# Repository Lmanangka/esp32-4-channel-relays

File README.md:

# PCB Design for 4-Channel Relays Based on ESP32-WROOM-32 Module

This repository contains the PCB design files, schematic, and 3D model image
for a 4-channel relay board based on the ESP32-WROOM-32 module. The board is
designed for controlling various electronic devices such as light, fans,
motors, and more.

## Features

- Four independently controllable 5V relays.
- ESP32-WROOM-32 module for wireless connectivity and easy programming.
- Terminal block for easy integration to the electronic devices.
- USB TYPE-C connector for power and programming
- Small form factor for easy integration into any project.

## Repository Contents

- **PCB design files**: The KiCad project files for the PCB design.
- **Schematic**: The circuit diagram of the design.
- **3D model image**: A preview image of the 3D model of the board.

## PCB Design

The PCB design is created using KiCad, an open-source software suite for
electronic design automation(EDA). The design files include the Schematic, the
PCB layout, and the Gerber files required for manufacturing.

The board include four 5V relays, each of which is controlled by a GPIO pin of
the ESP32-WROOM-32 module. The module is also responsible for wireless
connectivity and easy programming of the board. Terminal blocks are provided
for easy connection to the electronic devices. The board also includes a USB
TYPE-C connector for power and programming, providing a more robust and
versatile interface than traditional USB connectors.

## Schematic

The Schematic shows the circuit diagram of the design, including the
ESP32-WROOM-32 module, the relays, and the other components of the board.

## 3D Model Image

The 3D model image provides a preview of what the board looks like in a 3D view.
This can be usefule for visualizing the board and how it will fit into your
project.

## License

This design is released under the CERN Open Hardware License Version 2 - Permissive.
You are free to use, modify, and distribute the design as long as you include
the license file in your distribution. See the [LICENSE](https://github.com/Lmanangka/esp32-4-channel-relays/blob/main/LICENSE)
file for details.

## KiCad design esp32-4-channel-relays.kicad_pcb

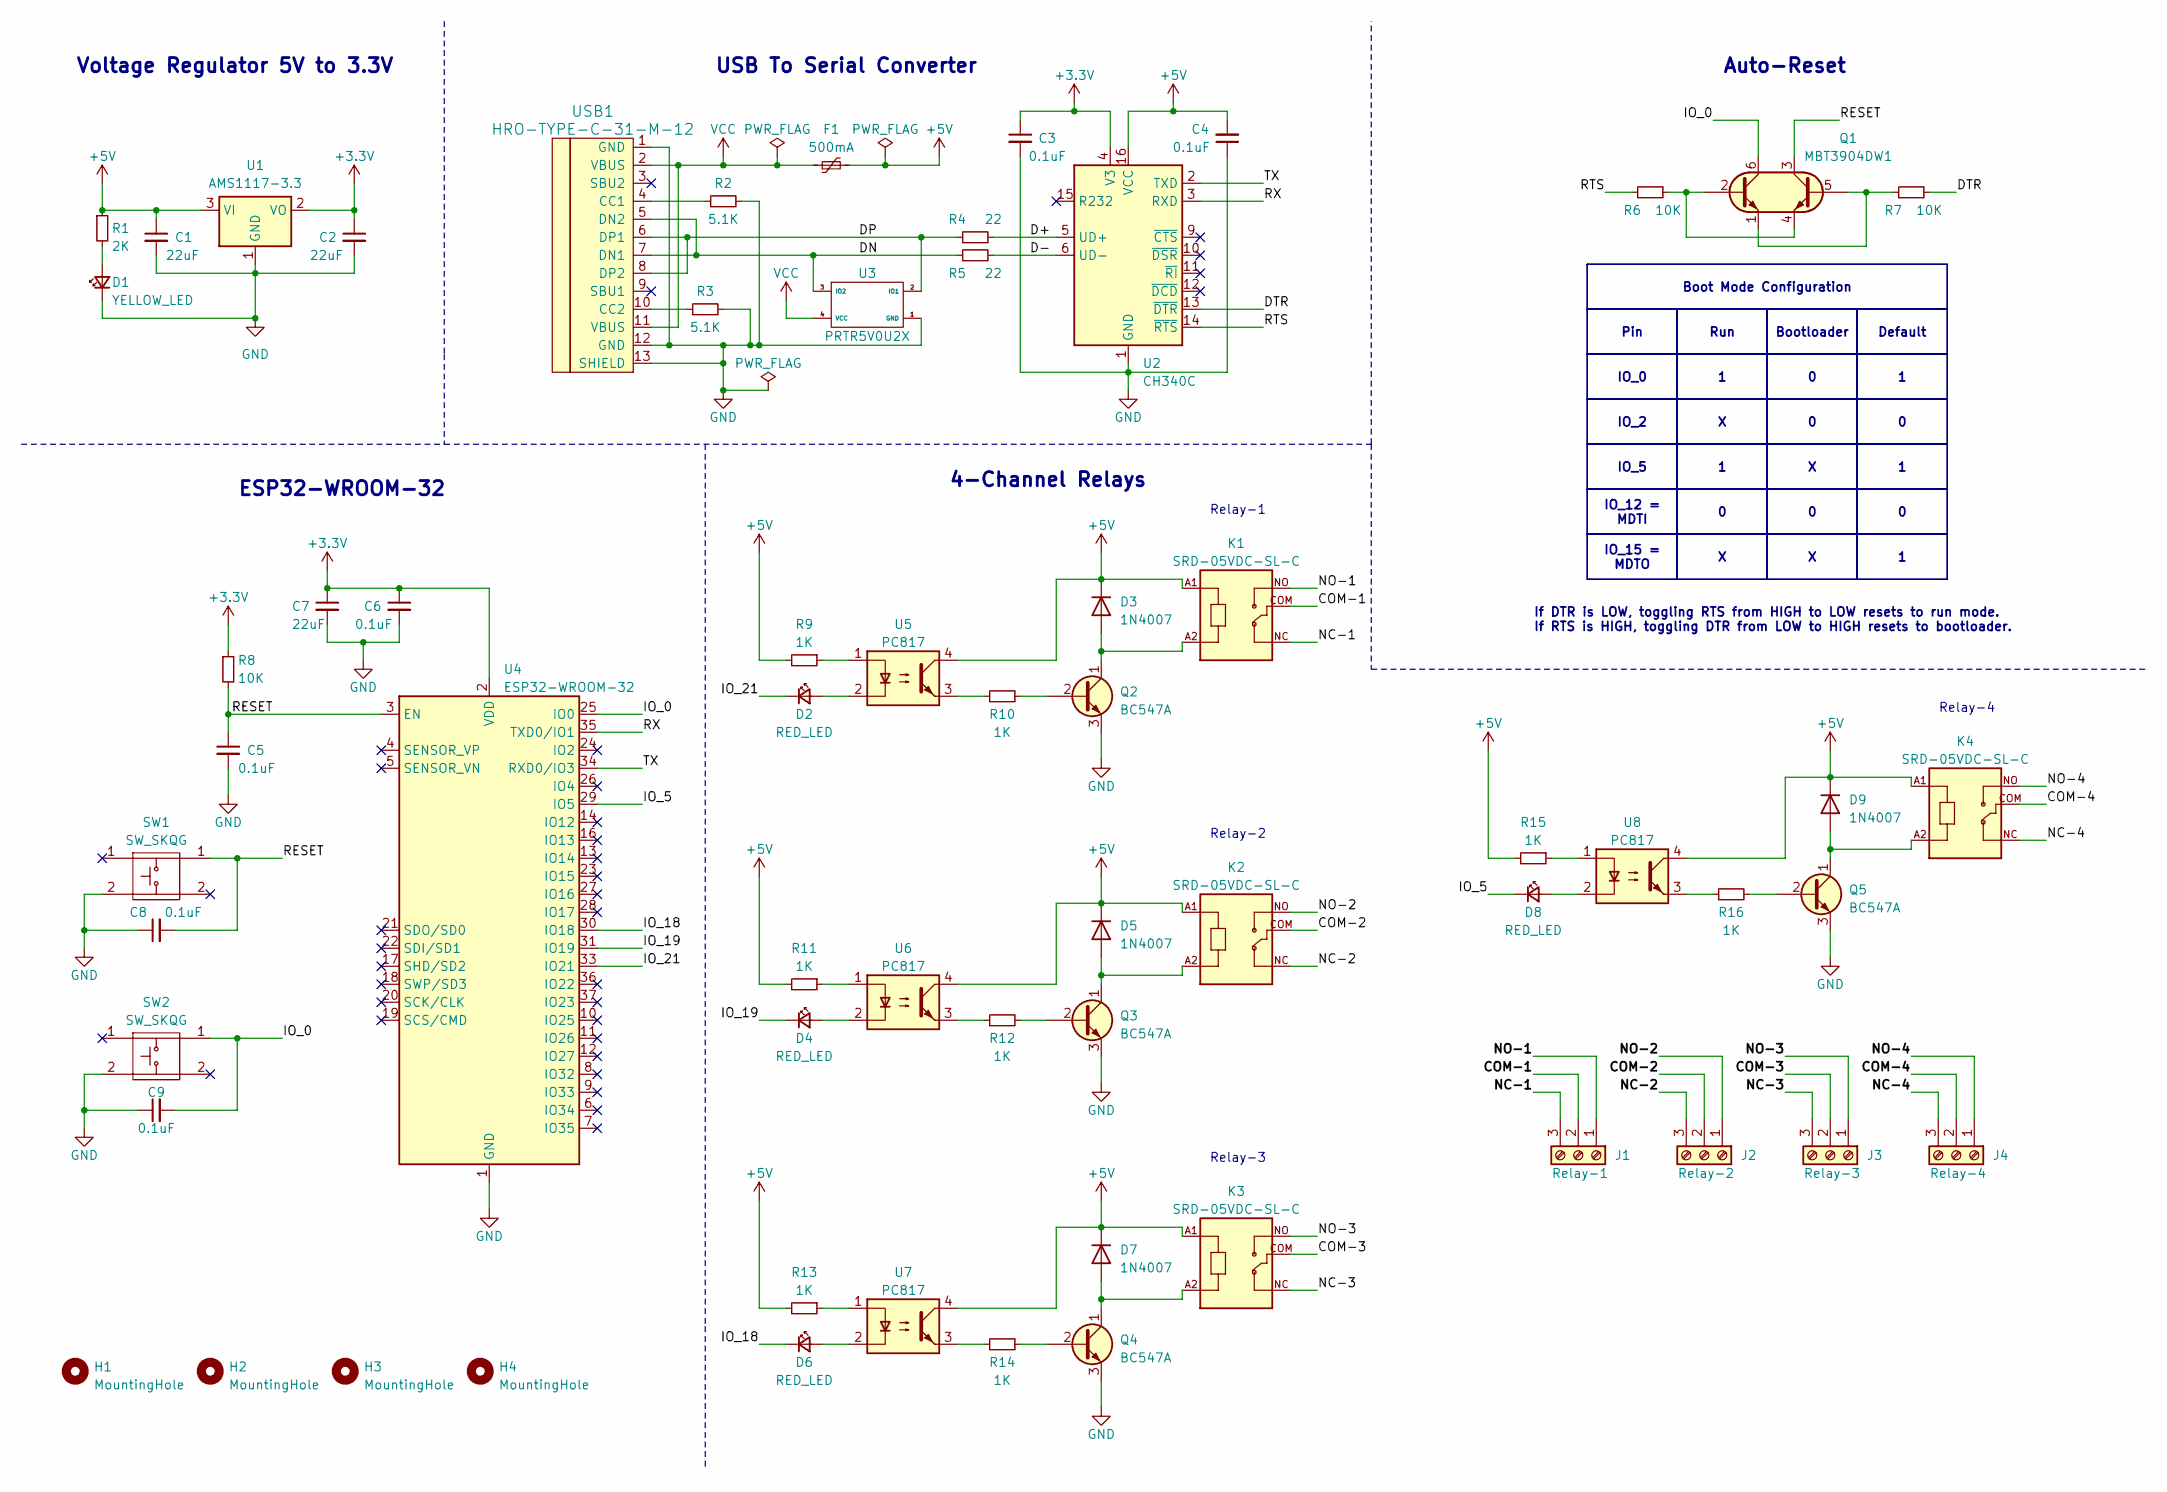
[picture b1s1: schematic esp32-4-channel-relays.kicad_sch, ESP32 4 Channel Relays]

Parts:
C1, C2, C7: 22uF; C_0805_2012Metric_Pad1.18x1.45mm_HandSolder
C3, C4, C5, C6, C8, C9: 0.1uF; C_0805_2012Metric_Pad1.18x1.45mm_HandSolder
D1: YELLOW_LED; LED_0805_2012Metric_Pad1.15x1.40mm_HandSolder
D2, D4, D6, D8: RED_LED; LED_0805_2012Metric_Pad1.15x1.40mm_HandSolder
D3, D5, D7, D9: 1N4007; D_MELF_Handsoldering
F1: 500mA; Fuse_1206_3216Metric_Pad1.42x1.75mm_HandSolder
H1, H2, H3, H4: MountingHole; MountingHole_3.2mm_M3
J1: Relay-1; TerminalBlock_Phoenix_MKDS-1,5-3-5.08_1x03_P5.08mm_Horizont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
J2: Relay-2; TerminalBlock_Phoenix_MKDS-1,5-3-5.08_1x03_P5.08mm_Horizont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
J3: Relay-3; TerminalBlock_Phoenix_MKDS-1,5-3-5.08_1x03_P5.08mm_Horizont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
J4: Relay-4; TerminalBlock_Phoenix_MKDS-1,5-3-5.08_1x03_P5.08mm_Horizont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
K1, K2, K3, K4: SRD-05VDC-SL-C; RELAY_SRD-05VDC-SL-C
Q1: MBT3904DW1; SOT-363_SC-70-6_Handsoldering
Q2, Q3, Q4, Q5: BC547A; TSOT-23_HandSoldering
R1: 2K; R_0805_2012Metric_Pad1.20x1.40mm_HandSolder
R2, R3: 5.1K; R_0805_2012Metric_Pad1.20x1.40mm_HandSolder
R4, R5: 22; R_0805_2012Metric_Pad1.20x1.40mm_HandSolder
R6, R7, R8: 10K; R_0805_2012Metric_Pad1.20x1.40mm_HandSolder
R9, R10, R11, R12, R13, R14, R15, R16: 1K; R_0805_2012Metric_Pad1.20x1.40mm_HandSolder
SW1, SW2: SW_SKQG; SW_SPST_SKQG_WithStem
U1: AMS1117-3.3; SOT-223-3_TabPin2
U2: CH340C; SOIC-16_3.9x9.9mm_P1.27mm
U3: PRTR5V0U2X; SOT-143_Handsoldering
U4: ESP32-WROOM-32
U5, U6, U7, U8: PC817; SMDIP-4_W7.62mm
USB1: HRO-TYPE-C-31-M-12; HRO-TYPE-C-31-M-12-HandSoldering

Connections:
+3.3V: C2.1, C3.1, C6.1, C7.1, R8.1, U1.2 (VO), U2.4 (V3), U4.2 (VDD)
+5V: C1.1, C4.2, D3.1 (K), D5.1 (K), D7.1 (K), D9.1 (K), F1.2, K1.A1, K2.A1, K3.A1, K4.A1, R1.1, R9.2, R11.2, R13.2, R15.2, U1.3 (VI), U2.16 (VCC), U5.4, U6.4, U7.4, U8.4
/COM-1: J1.2, K1.COM
/COM-2: J2.2, K2.COM
/COM-3: J3.2, K3.COM
/COM-4: J4.2, K4.COM
/D+: R4.2, U2.5 (UD+)
/D-: R5.2, U2.6 (UD-)
/DN: R5.1, U3.3 (IO2), USB1.5 (DN2), USB1.7 (DN1)
/DP: R4.1, U3.2 (IO1), USB1.6 (DP1), USB1.8 (DP2)
/DTR: R7.2, U2.13 (~DTR)
/IO_0: C9.2, Q1.6 (C1), SW2.1, U4.25 (IO0)
/IO_5: D8.1 (K), U4.29 (IO5)
/IO_18: D6.1 (K), U4.30 (IO18)
/IO_19: D4.1 (K), U4.31 (IO19)
/IO_21: D2.1 (K), U4.33 (IO21)
/NC-1: J1.3, K1.NC
/NC-2: J2.3, K2.NC
/NC-3: J3.3, K3.NC
/NC-4: J4.3, K4.NC
/NO-1: J1.1, K1.NO
/NO-2: J2.1, K2.NO
/NO-3: J3.1, K3.NO
/NO-4: J4.1, K4.NO
/RESET: C5.1, C8.2, Q1.3 (C2), R8.2, SW1.1, U4.3 (EN)
/RTS: R6.1, U2.14 (~RTS)
/RX: U2.3 (RXD), U4.35 (TXD0/IO1)
/TX: U2.2 (TXD), U4.34 (RXD0/IO3)
GND: C1.2, C2.2, C3.2, C4.1, C5.2, C6.2, C7.2, C8.1, C9.1, D1.1 (K), Q2.3 (E), Q3.3 (E), Q4.3 (E), Q5.3 (E), R2.2, R3.2, SW1.2, SW2.2, U1.1 (GND), U2.1 (GND), U3.1 (GND), U4.1 (GND), U4.15 (GND), U4.38 (GND), U4.39 (GND), USB1.1 (GND), USB1.12 (GND), USB1.13 (SHIELD)
unnamed: D1.2 (A), R1.2
unnamed: D2.2 (A), U5.2
unnamed: D3.2 (A), K1.A2, Q2.1 (C)
unnamed: D4.2 (A), U6.2
unnamed: D5.2 (A), K2.A2, Q3.1 (C)
unnamed: D6.2 (A), U7.2
unnamed: D7.2 (A), K3.A2, Q4.1 (C)
unnamed: D8.2 (A), U8.2
unnamed: D9.2 (A), K4.A2, Q5.1 (C)
unnamed: Q1.2 (B1), Q1.4 (E2), R6.2
unnamed: Q1.1 (E1), Q1.5 (B2), R7.1
unnamed: Q2.2 (B), R10.2
unnamed: Q3.2 (B), R12.2
unnamed: Q4.2 (B), R14.2
unnamed: Q5.2 (B), R16.2
unnamed: R9.1, U5.1
unnamed: R10.1, U5.3
unnamed: R11.1, U6.1
unnamed: R12.1, U6.3
unnamed: R13.1, U7.1
unnamed: R14.1, U7.3
unnamed: R15.1, U8.1
unnamed: R16.1, U8.3
unnamed: R2.1, USB1.4 (CC1)
unnamed: R3.1, USB1.10 (CC2)
VCC: F1.1, U3.4 (VCC), USB1.2 (VBUS), USB1.11 (VBUS)

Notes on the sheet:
Default
IO_2
IO_15 = MDTO
Bootloader
IO_0
IO_12 = MDTI
Run
Boot Mode Configuration
IO_5
Pin
Voltage Regulator 5V to 3.3V
4-Channel Relays
Relay-1
Relay-4
Relay-3
Relay-2
Auto-Reset
ESP32-WROOM-32
If DTR is LOW, toggling RTS from HIGH to LOW resets to run mode. If RTS is HIGH, toggling DTR from LOW to HIGH resets to bootloader.
USB To Serial Converter

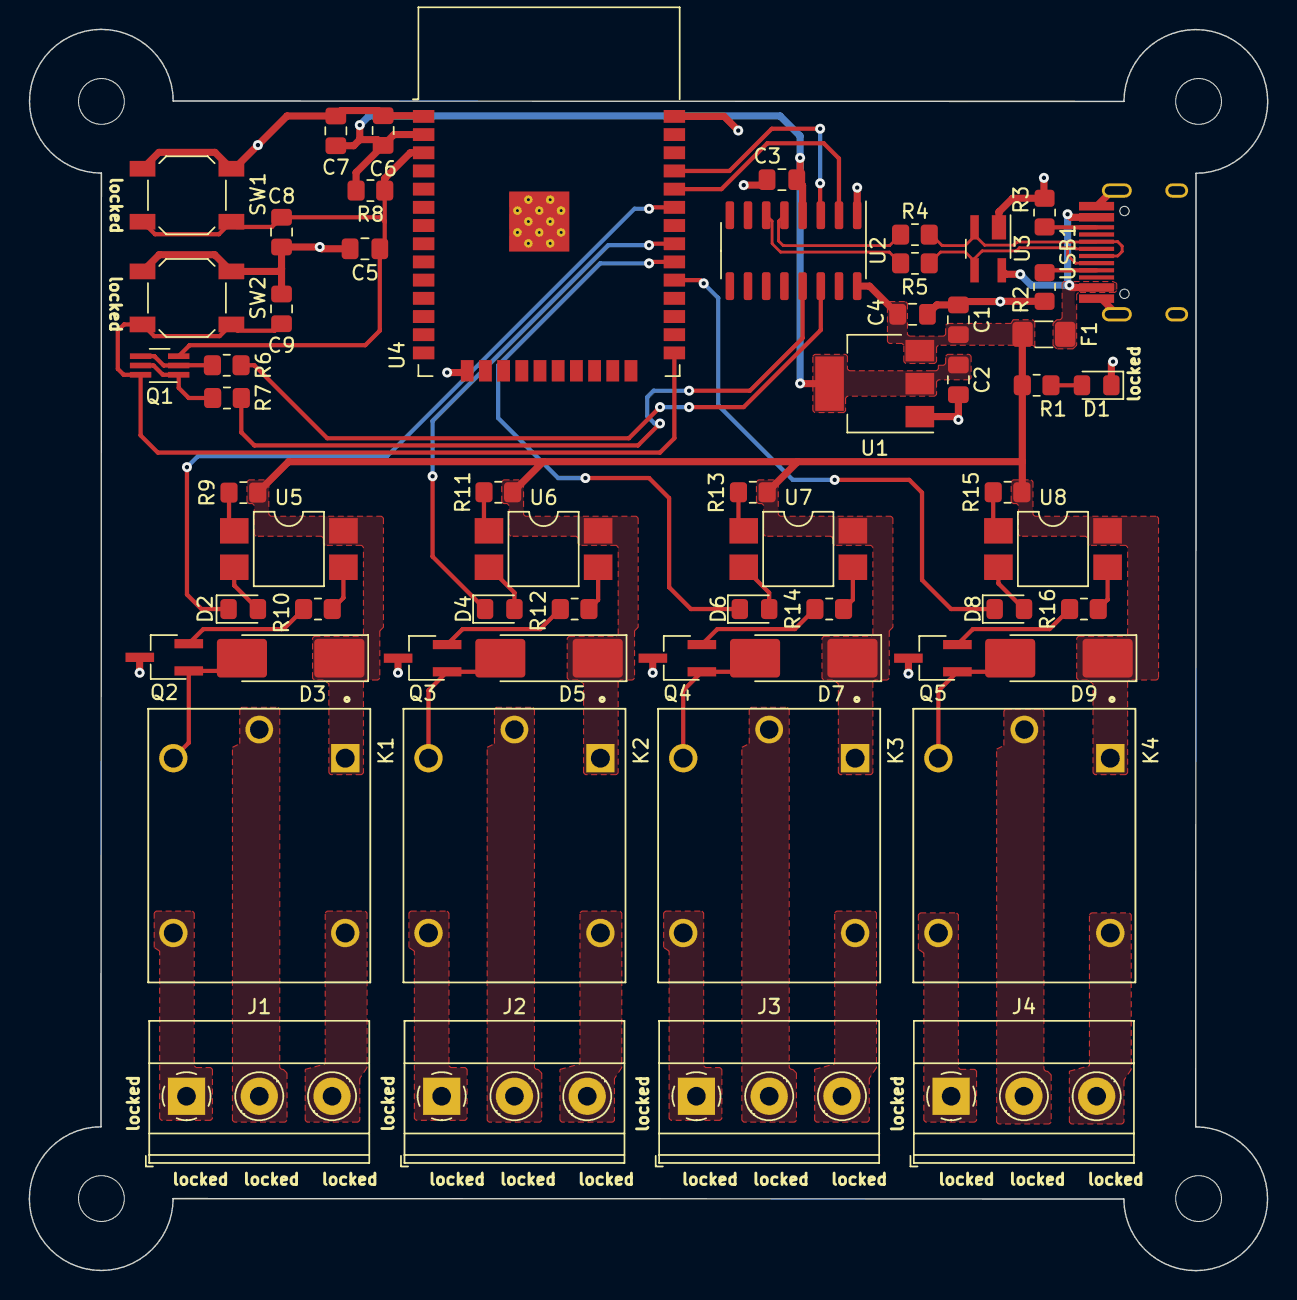
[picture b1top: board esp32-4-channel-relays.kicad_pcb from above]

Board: 2 copper layers, 86.4 x 86.6 mm, 63 parts (0 on the bottom side), 55 nets.

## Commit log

2023-03-19 Add .gitignore
2023-03-19 Add project library
2023-03-19 Add empty KiCad files
2023-03-19 Add esp32-4-channel-relays-backups to gitignore
2023-03-19 Add voltage regulator 5V to 3.3V
2023-03-19 Add USB to serial converter
2023-03-19 Add auto-reset
2023-03-19 Add SW_SKQG as new symbol
2023-03-19 Add ESP32-WROOM-32 and reset button and boot button
2023-03-20 Update library add relay, optocoupler and transistor symbols
2023-03-20 Add 4-channel relays to the schematic
2023-03-20 Add screw terminal for relay output and wiring relay input to esp32 GPIO
2023-03-20 Add 3d model for USB Type-C and Relay 5V
2023-03-20 Add footprint for components other than resistors and capacitors
2023-03-20 Add project footprint library
2023-03-20 Assign footprint to project symbol library
2023-03-20 Assign footprints
2023-03-21 Load schematic to PCB Editor
2023-03-21 Make temporary edge cut and relays placement
2023-03-22 USB Type-C and Voltage regulator 3.3V placement
2023-03-22 ESP32, auto-reset and buttons placement also a little tweak to USB to serial converter placement
2023-03-22 Add mounting hole symbols and assign footprint
2023-03-22 Add mounting hole to pcb editor and redraw edgecut
2023-03-22 Add fill zone and routing VCC, 5V and 3.3V power
2023-03-22 Routing relays
2023-03-22 Routing Reset, Reset switch button and IO_0, IO_0 switch button
2023-03-22 Routing GND, RTS and DTR
2023-03-22 Reconnect relays to esp32 considering footprint placement
2023-03-22 Routing relays to esp32 and design rules check
2023-03-22 Add 3d model for switch button and link it to switch button footprint
2023-03-23 Design rules check and lock components
2023-03-23 Add Labels for relays, switch button and LED power indicator
2023-03-27 Update page setting
2023-03-27 Add image
2023-03-27 Add schematic
2023-03-27 Add LICENSE
